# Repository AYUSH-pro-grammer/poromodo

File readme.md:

# Poromodo Timer

A mini pomodoro timer powered by a battery. This was designed using KiCad to create a custom PCB. A small case was designed to house the timer board, OLED and movement sensor. The aim of this project is to create an easy to use and easy to build timer that can rotate the display depending on how it is held.

The design includes a 2S Li-Ion battery, 5V buck converter, 0.96 inch OLED and GY-521 module with MPU-6050. The XIAO manages the timer logic and provides Wi-Fi and Bluetooth Low Energy for future features.

## How it works

The battery pack provides approximately 7.4V (8.4V fully charged). This is passed through a power switch and P Channel MOSFET anti polarity protection circuit, then into a 5V Buck converter (AP63205). A Schottky diode is used to feed the 5V rail to the XIAO's VBUS pin. This also helps to prevent USB power being fed into the Buck Converter.

The XIAO has an onboard regulator that provides a 3.3V rail to provide power to the OLED and GY-521 motion sensing module. The OLED uses I2C to communicate with the XIAO. The MPU-6050 uses the same I2C line to send orientation data. This can be used by the firmware to rotate the display. A resistor divider is used to step down the battery voltage to be passed to the ADC. The buttons, status LED and buzzer are all connected to individual GPIO pins. The buzzer is turned on using an NPN transistor.

```text
[ 2S Li-ion Battery ]
          |
          v
[ Power Switch + Reverse-Polarity Protection ]
          |
          v
[ AP63205 Buck Converter ] -- 5 V --> [ Schottky Diode ]
                                               |
                                               v
                                      [ XIAO ESP32-C3 ]
                                         |         |
                                      3.3 V       GPIO / ADC
                                         |         |
                             +-----------+         +------------------+
                             |           |         |        |         |
                             v           v         v        v         v
                          [ OLED ]   [ GY-521 ] [ Buttons ] [ LED ] [ Buzzer ]
                              \\___________ I2C ___________//
```

## Main features

Seeed XIAO ESP32-C3 (Wi-Fi + BLE) micro controller module
2S Li-ion battery input
AP63205 5V buck converter
AO3401A P-channel MOSFET used for reverse polarity protection
0.96" 128x64 SSD1306 I2C OLED display
GY-521 MPU-6050 accelerometer and gyroscope module
Resistor voltage divider for battery sensing
Two buttons for user Input
Status LED
Passive buzzer controlled by transistor
Double sided PCB around 36x82mm
Two part 3D printable housing

## Images

### Schematic

### PCB layout

### PCB 3D view

### Enclosure

### PCB quotation

## Assembly guide

The design data, manufacturing data, and housing designs can be found here. Before assembly ensure that component footprints match, and that the pin layout of the connectors matches the OLED and GY-521 modules you have. Different variants may show different pin outs.

PCB Preparation: Order the PCB by using gerber.zip, or each file in gerber/. Ensure that the board outline, drilling and layer detection all look correct.
Board Inspection: Check the board has no obvious damage. Check the pads, connectors, and solder mask. Check for any unexpected short circuits using a multi-meter.
Power Assembly: Construct the battery input, AO3401A protection circuit, AP63205 regulator, inductor, and associated capacitors. Ensure that the MOSFET and regulator are placed correctly (Check pin out of MOSFET and regulator from datasheet).
XIAO Module: Place the module onto the PCB ensuring that the module matches the footprint on the PCB. Check all solder joints. Ensure there are no solder bridges between adjacent pads.
Connector & Peripheral Assembly: Attach the OLED and GY-521 sockets, buttons, LED, buzzer, and battery connector. Check the header pins on the OLED match GND, 3V3, SCL, SDA. Check this matches the display module you have.
Power Rails: Double check everything looks good. If possible use a current limited bench PSU to ensure that the 5V and 3.3V rails are correct.
Housing Assembly: The housing can be found in the 3d/ directory. This contains STEP assembly, Fusion 360 archive, and print ready STLs. Have a test fit of the PCB and OLED. The holes are designed to take M3 hardware.
Battery Connection: Use an appropriate 2S protected battery pack. Ensure you use a proper 2S charger. A fully charged 2S battery will be 8.4V. The XIAO will not use the 1 cell battery input.

## Firmware upload

The `firmware/` directory contains separate Arduino sketches. They are intended to be uploaded one at a time while bringing up and testing the board.

| Sketch | Purpose |
|---|---|
| `01_hello_pins.ino` | Basic GPIO and pin checks |
| `02_i2c_scanner.ino` | Scan the I2C bus for connected devices |
| `03_oled_basics.ino` | Basic OLED initialization and display test |
| `04_oled_animations.ino` | OLED animation tests |
| `05_mpu_config.ino` | MPU-6050 configuration and sensor readings |
| `06_auto_rotate.ino` | Display rotation based on sensor orientation |
| `07_buzzer_buttons_led.ino` | Test the buzzer, buttons and status LED |
| `08_battery_monitor.ino` | Read the battery-voltage divider using the ADC |
| `09_pomodoro_demo.ino` | Combined Pomodoro timer demonstration |

### Upload steps

Install the Arduino IDE.
From within the Boards Manager, install the ESP32 board package from Espressif.
Connect the XIAO ESP32-C3 via USB data cable.
Open one of the .ino files located in firmware/.
Select the board type as XIAO_ESP32C3 and select the correct serial port.
Ensure that all libraries required by the sketch have been installed. These can be seen at the top of each source file.
Click the verify button to compile the sketch. Then click upload.
If the sketch uses serial output, open the Serial Monitor and select the baud rate set in the sketch.

We will start by using 01_hello_pins.ino. Once we know that the I2C and OLED are working we can move onto the sensor and full demo. Each of these are individual test programs so uploading a new sketch will overwrite the previous firmware on the XIAO.

## Repository contents

```text
.
├── 3d/              # STEP assembly and printable enclosure files
├── firmware/        # Arduino test sketches and Pomodoro demo
├── gerber/          # PCB Gerber and drill files
├── gerber.zip       # Fabrication upload archive
├── images/          # Main project images
├── kicad/           # KiCad schematic and PCB project
├── bom.csv          # Component list, prices and purchase links
└── README.md
```

## Components and BOM

| Qty | Component | Unit price (USD) | Total (USD) | Buy |
|---:|---|---:|---:|---|
| 1 | XIAO ESP32-C3 (U1) | $5.39 | $5.39 | [RobotShop](https://www.robotshop.com/products/seeedstudio-xiao-esp32c3-tiny-mcu-w-wi-fi-ble) |
| 1 | AP63205WU-7 buck converter, 5 V 2 A, TSOT-26 (U2) | $0.25 | $0.25 | [LCSC](https://www.lcsc.com/product-detail/C2071056.html) |
| 1 | Inductor 4.7 µH, Bourns SRN6045TA-4R7M (L1) | $0.60 | $0.60 | [DigiKey](https://www.digikey.fi/en/products/detail/bourns-inc/SRN6045TA-4R7M/6155104) |
| 2 | Capacitor 22 µF 25 V X5R 1206 (C1, C2) | $0.0595 | $0.12 | [LCSC](https://www.lcsc.com/product-detail/C12891.html) |
| 1 | Capacitor 10 µF 1206 (C4) | $0.05 | $0.05 | [LCSC search](https://www.lcsc.com/search?q=10uF+1206+25V+X5R) |
| 2 | Capacitor 100 nF 0805 (C3, C5) | $0.01 | $0.02 | [LCSC search](https://www.lcsc.com/search?q=100nF+0805+50V) |
| 1 | Resistor 1 kΩ 0805 (R1) | $0.01 | $0.01 | [LCSC search](https://www.lcsc.com/search?q=1k+0805+resistor) |
| 1 | Resistor 100 kΩ 0805 (R2, battery divider top) | $0.01 | $0.01 | [LCSC search](https://www.lcsc.com/search?q=100k+0805+resistor) |
| 1 | Resistor 33 kΩ 0805 (R3, battery divider bottom) | $0.01 | $0.01 | [LCSC search](https://www.lcsc.com/search?q=33k+0805+resistor) |
| 1 | Resistor 470 Ω 0805 (R4) | $0.01 | $0.01 | [LCSC search](https://www.lcsc.com/search?q=470+ohm+0805+resistor) |
| 1 | Schottky diode SS34, SMA (D2) | $0.05 | $0.05 | [LCSC search](https://www.lcsc.com/search?q=SS34) |
| 1 | Diode 1N4148W, SOD-123 (D1, buzzer flyback) | $0.02 | $0.02 | [LCSC search](https://www.lcsc.com/search?q=1N4148W) |
| 1 | LED 0805 (D3) | $0.03 | $0.03 | [LCSC search](https://www.lcsc.com/search?q=led+0805) |
| 1 | NPN transistor MMBT3904, SOT-23 (Q1) | $0.02 | $0.02 | [LCSC search](https://www.lcsc.com/search?q=MMBT3904) |
| 1 | P-MOSFET AO3401A, SOT-23 (Q2) | $0.10 | $0.10 | [LCSC search](https://www.lcsc.com/search?q=AO3401A) |
| 1 | Passive buzzer 12 × 9.5 mm, Soberton WT-1209T (BZ1) | $1.15 | $1.15 | [DigiKey](https://www.digikey.com/en/products/detail/soberton-inc/WT-1209T/16384509) |
| 1 | GY-521 MPU6050 module (J4 socket) | $3.79 | $3.79 | [OpenELAB](https://openelab.com/products/mpu6050-gy521-six-axis-sensor) |
| 1 | 0.96-inch OLED 128 × 64 I2C SSD1306, 4-pin (J1 socket) | $6.89 | $6.89 | [ShillehTek](https://shillehtek.com/products/0-96-i2c-white-oled-display-module-4-pin-ssd1306) |
| 1 | Female pin socket 1 × 8, 2.54 mm (J4) | $0.15 | $0.15 | [LCSC search](https://www.lcsc.com/search?q=female+header+1x8+2.54) |
| 1 | Female pin socket 1 × 4, 2.54 mm (J1) | $0.10 | $0.10 | [LCSC search](https://www.lcsc.com/search?q=female+header+1x4+2.54) |
| 1 | Male pin header 1 × 2, 2.54 mm (SW2 footprint) | $0.05 | $0.05 | [LCSC search](https://www.lcsc.com/search?q=pin+header+1x2+2.54) |
| 1 | Slide or rocker switch SPST, wired to SW2 | $0.50 | $0.50 | [LCSC search](https://www.lcsc.com/search?q=slide+switch+SPDT) |
| 2 | Tactile switch 6 × 6 mm through-hole (SW1, SW3) | $0.017 | $0.03 | [LCSC](https://www.lcsc.com/product-detail/C480288.html) |
| 1 | JST PH 2-pin header B2B-PH-K-S (J2) | $0.30 | $0.30 | [DigiKey](https://www.digikey.nl/en/products/detail/jst-sales-america-inc/B2B-PH-K-S/926611) |
| 1 | 2S Li-ion battery pack, 7.4 V, JST PH 2.0 plug | $9.00 | $9.00 | [DigiKey search](https://www.digikey.com/en/search?keywords=7.4V%20li-ion%20battery%20pack%20JST%20PH) |
| 1 | M3 screws and standoffs (4 sets) | $1.50 | $1.50 | [LCSC search](https://www.lcsc.com/search?q=M3+standoff) |
| 1 | PCB, 2-layer, 36 × 82 mm, 1.6 mm, green (5 pieces) | $4.00 | $4.00 | [JLCPCB](https://jlcpcb.com/) |
| 1 | PCB shipping, UPS Express Saver (2–4 business days) | $26.60 | $26.60 | [JLCPCB](https://jlcpcb.com/) |
|  | **Total procurement estimate** |  | **$60.75** |  |

## PCB manufacturing files

The `gerber/` folder contains the exported copper, solder mask, paste, silkscreen, board outline and drill files. The `gerber.zip` archive is provided for uploading to a PCB manufacturer. Review the fabrication preview and confirm the detected board outline, layer count and drill files before ordering.

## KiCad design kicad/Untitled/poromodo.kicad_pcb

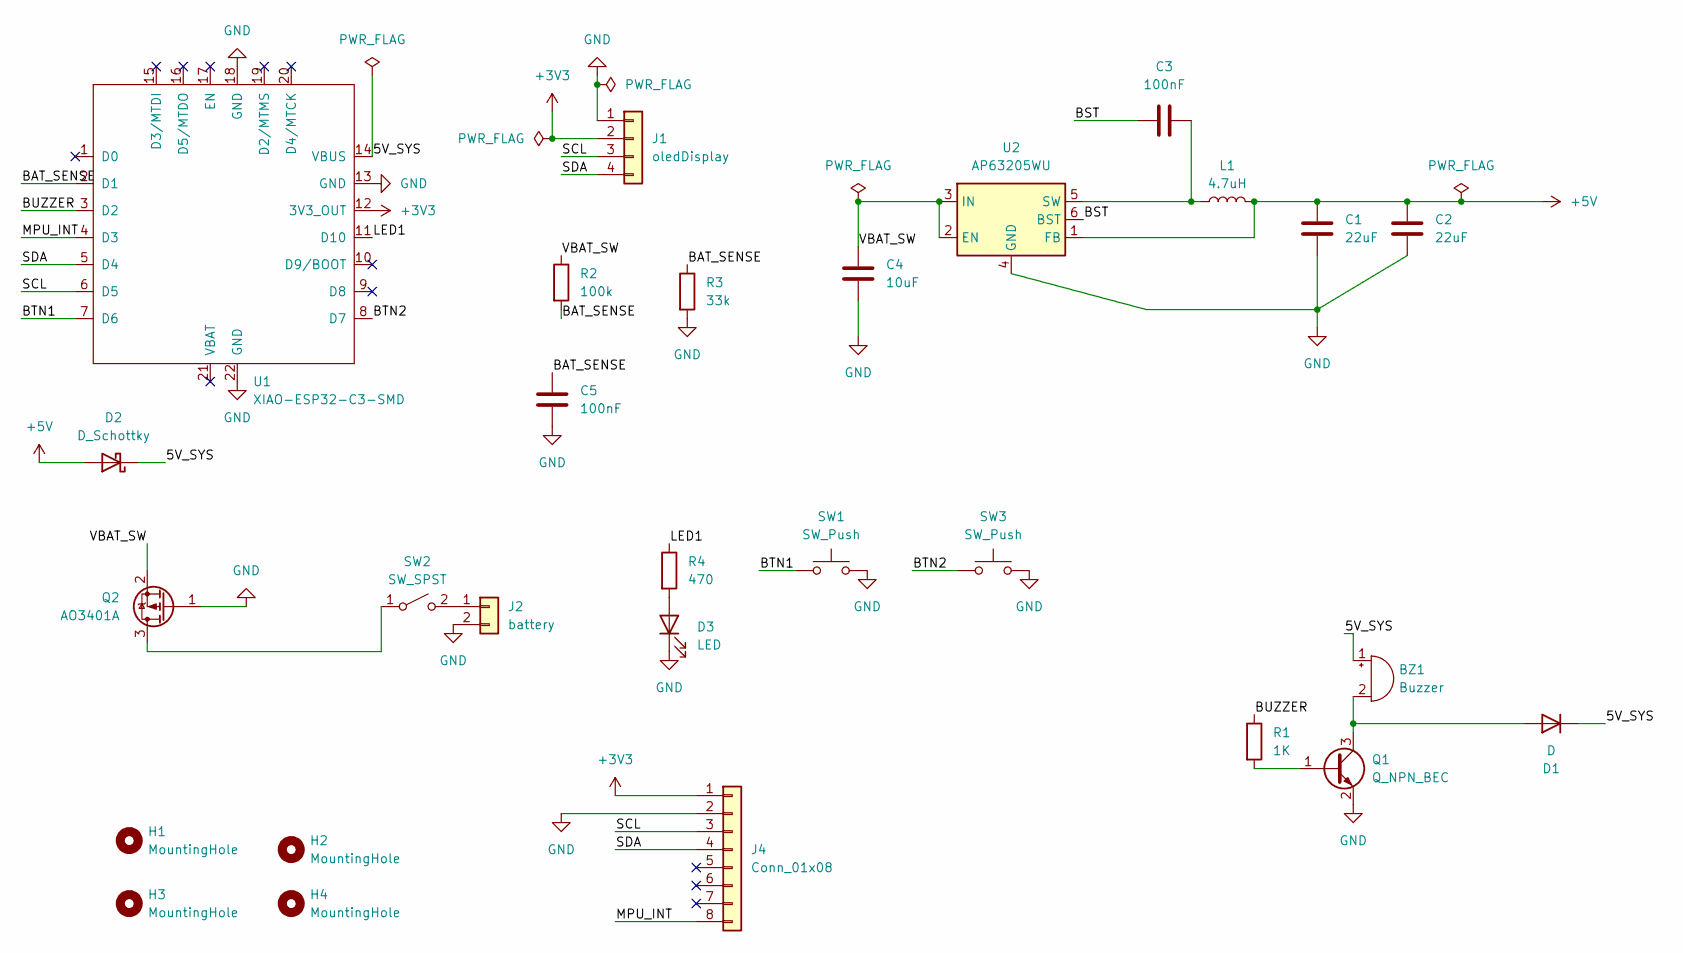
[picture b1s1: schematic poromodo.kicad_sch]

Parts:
BZ1: Buzzer; Buzzer_12x9.5RM7.6
C1, C2: 22uF; C_1206_3216Metric
C3, C5: 100nF; C_0805_2012Metric
C4: 10uF; C_1206_3216Metric
D1: D; D_SOD-123
D2: D_Schottky; D_SMA
D3: LED; LED_0805_2012Metric
H1, H2, H3, H4: MountingHole; MountingHole_3.2mm_M3
J1: oledDisplay; PinSocket_1x04_P2.54mm_Vertical
J2: battery; JST_PH_B2B-PH-K_1x02_P2.00mm_Vertical
J4: Conn_01x08; PinSocket_1x08_P2.54mm_Vertical
L1: 4.7uH; L_Bourns_SRN6045TA
Q1: Q_NPN_BEC; SOT-23
Q2: AO3401A; SOT-23
R1: 1K; R_0805_2012Metric
R2: 100k; R_0805_2012Metric
R3: 33k; R_0805_2012Metric
R4: 470; R_0805_2012Metric
SW1, SW3: SW_Push; SW_PUSH_6mm
SW2: SW_SPST; PinHeader_1x02_P2.54mm_Vertical
U1: XIAO-ESP32-C3-SMD
U2: AP63205WU; TSOT-23-6

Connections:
+3V3: J1.2, J4.1, U1.12 (3V3_OUT)
+5V: C1.1, C2.1, D2.2 (A), L1.2, U2.1 (FB)
/5V_SYS: BZ1.1 (+), D1.1 (K), D2.1 (K), U1.14 (VBUS)
/BAT_SENSE: C5.1, R2.2, R3.1, U1.2 (D1)
/BST: C3.1, U2.6 (BST)
/BTN1: SW1.1, U1.7 (D6)
/BTN2: SW3.1, U1.8 (D7)
/BUZZER: R1.1, U1.3 (D2)
/LED1: R4.1, U1.11 (D10)
/MPU_INT: J4.8, U1.4 (D3)
/SCL: J1.3, J4.3, U1.6 (D5)
/SDA: J1.4, J4.4, U1.5 (D4)
/VBAT_SW: C4.1, Q2.2 (S), R2.1, U2.2 (EN), U2.3 (IN)
GND: C1.2, C2.2, C4.2, C5.2, D3.1 (K), J1.1, J2.2, J4.2, Q1.2 (E), Q2.1 (G), R3.2, SW1.2, SW3.2, U1.13 (GND), U1.18 (GND), U1.22 (GND), U2.4 (GND)
unnamed: BZ1.2 (-), D1.2 (A), Q1.3 (C)
unnamed: D3.2 (A), R4.2
unnamed: J2.1, SW2.2 (B)
unnamed: Q1.1 (B), R1.2
unnamed: Q2.3 (D), SW2.1 (A)
unnamed: C3.2, L1.1, U2.5 (SW)

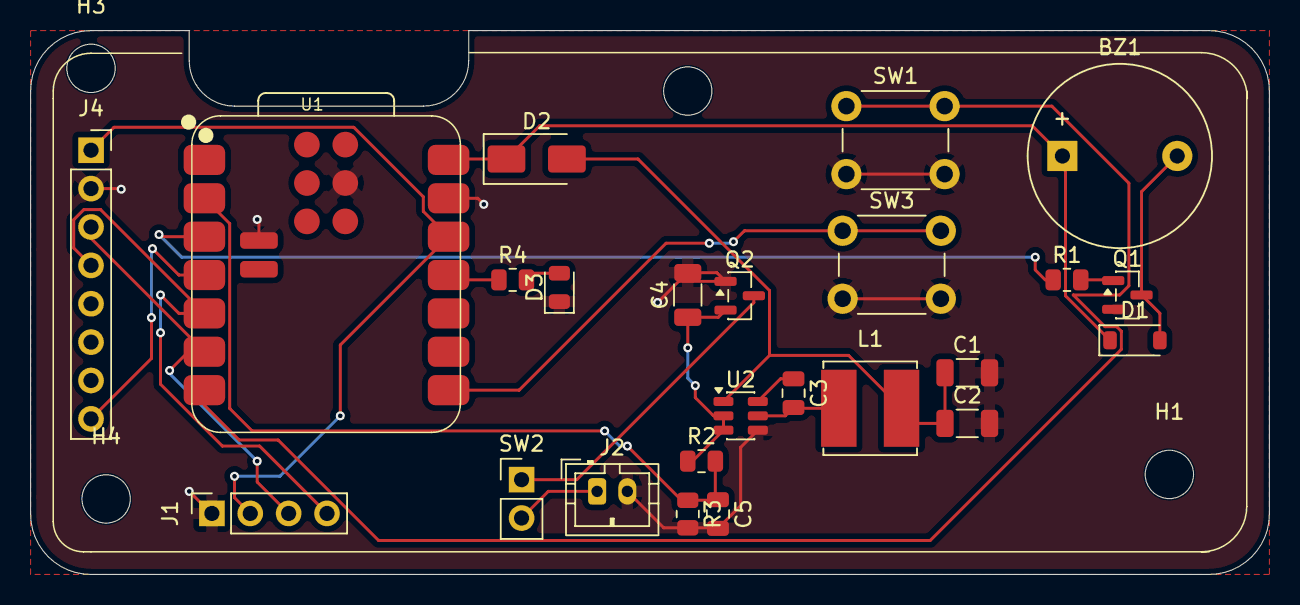
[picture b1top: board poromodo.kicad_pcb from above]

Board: 2 copper layers, 82.0 x 36.0 mm, 28 parts (0 on the bottom side), 20 nets.

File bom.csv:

Name,Quantity,Unit price (USD),Total (USD),URL to buy,Notes
XIAO ESP32-C3 (U1),1,5.39,5.39,https://www.robotshop.com/products/seeedstudio-xiao-esp32c3-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,Seeed XIAO ESP32C3 board only. price checked on seller page
"AP63205WU-7 buck converter, 5V 2A, TSOT-26 (U2)",1,0.25,0.25,https://www.lcsc.com/product-detail/C2071056.html,"LCSC 'from' price, small quantities cost a little more. price checked on seller page"
"Inductor 4.7uH, Bourns SRN6045TA-4R7M (L1)",1,0.60,0.60,https://www.digikey.fi/en/products/detail/bourns-inc/SRN6045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,"Out of stock at DigiKey (18 week lead time). Use a 6x6 mm 4.7uH shielded inductor with the same land pattern. estimate, check at checkout"
"Capacitor 22uF 25V X5R 1206 (C1, C2)",2,0.0595,0.12,https://www.lcsc.com/product-detail/C12891.html,Samsung CL31A226KAHNNNE. LCSC 'from' price. price checked on seller page
Capacitor 10uF 1206 (C4),1,0.05,0.05,https://www.lcsc.com/search?q=10uF+1206+25V+X5R,"Use 16V or higher. estimate, check at checkout"
"Capacitor 100nF 0805 (C3, C5)",2,0.01,0.02,https://www.lcsc.com/search?q=100nF+0805+50V,"Parts are very cheap but often sold in packs. estimate, check at checkout"
Resistor 1k 0805 (R1),1,0.01,0.01,https://www.lcsc.com/search?q=1k+0805+resistor,"estimate, check at checkout"
"Resistor 100k 0805 (R2, battery divider top)",1,0.01,0.01,https://www.lcsc.com/search?q=100k+0805+resistor,"estimate, check at checkout"
"Resistor 33k 0805 (R3, battery divider bottom)",1,0.01,0.01,https://www.lcsc.com/search?q=33k+0805+resistor,"estimate, check at checkout"
Resistor 470 ohm 0805 (R4),1,0.01,0.01,https://www.lcsc.com/search?q=470+ohm+0805+resistor,"estimate, check at checkout"
"Schottky diode SS34, SMA (D2)",1,0.05,0.05,https://www.lcsc.com/search?q=SS34,"estimate, check at checkout"
"Diode 1N4148W, SOD-123 (D1, buzzer flyback)",1,0.02,0.02,https://www.lcsc.com/search?q=1N4148W,"estimate, check at checkout"
LED 0805 (D3),1,0.03,0.03,https://www.lcsc.com/search?q=led+0805,"estimate, check at checkout"
"NPN transistor MMBT3904, SOT-23 (Q1)",1,0.02,0.02,https://www.lcsc.com/search?q=MMBT3904,"estimate, check at checkout"
"P-MOSFET AO3401A, SOT-23 (Q2)",1,0.10,0.10,https://www.lcsc.com/search?q=AO3401A,"estimate, check at checkout"
"Passive buzzer 12x9.5 mm, Soberton WT-1209T (BZ1)",1,1.15,1.15,https://www.digikey.com/en/products/detail/soberton-inc/WT-1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,DigiKey qty 1 price. Check the datasheet for 7.6 mm pin pitch before ordering. price checked on seller page
GY-521 MPU6050 module (J4 socket),1,3.79,3.79,https://openelab.com/products/mpu6050-gy521-six-axis-sensor,Listed as sold out / pre-order (10-20 working days). Check other sellers. price checked on seller page
"0.96 inch OLED 128x64 I2C SSD1306, 4 pin (J1 socket)",1,6.89,6.89,https://shillehtek.com/products/0-96-i2c-white-oled-display-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,"Pin order differs between modules. Check it matches J1 (GND, 3V3, SCL, SDA) or the module will not work. price checked on seller page"
"Female pin socket 1x8, 2.54 mm (J4)",1,0.15,0.15,https://www.lcsc.com/search?q=female+header+1x8+2.54,"estimate, check at checkout"
"Female pin socket 1x4, 2.54 mm (J1)",1,0.10,0.10,https://www.lcsc.com/search?q=female+header+1x4+2.54,"estimate, check at checkout"
"Male pin header 1x2, 2.54 mm (SW2 footprint)",1,0.05,0.05,https://www.lcsc.com/search?q=pin+header+1x2+2.54,"estimate, check at checkout"
"Slide or rocker switch SPST, to wire to SW2",1,0.50,0.50,https://www.lcsc.com/search?q=slide+switch+SPDT,"estimate, check at checkout"
"Tactile switch 6x6 mm through hole (SW1, SW3)",2,0.017,0.03,https://www.lcsc.com/product-detail/C480288.html,"XKB TC-1102-B-I-B, LCSC 'from' price, low stock (280). Pick a height that fits your case. price checked on seller page"
JST PH 2-pin header B2B-PH-K-S (J2),1,0.30,0.30,https://www.digikey.nl/en/products/detail/jst-sales-america-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,"Battery pack needs the mating JST PH plug. estimate, check at checkout"
2S Li-ion battery pack 7.4V with JST PH 2.0 plug,1,9.00,9.00,https://www.digikey.com/en/search?keywords=7.4V%20li-ion%20b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,"Not checked. The connector is rated about 2 A. You also need a 2S charger. estimate, check at checkout"
M3 screws and standoffs (4 sets),1,1.50,1.50,https://www.lcsc.com/search?q=M3+standoff,"Mounting holes are 3.2 mm. estimate, check at checkout"
"PCB, 2 layer, 36x82 mm, 1.6 mm, green (5 pieces)",1,4.00,4.00,https://jlcpcb.com/,"JLCPCB cart price (special offer, 2 day build). See images/jlcpcb-cart.png. Upload gerber.zip"
"PCB shipping, UPS Express Saver (2-4 business days)",1,26.60,26.60,https://jlcpcb.com/,JLCPCB shipping estimate for 0.17 kg. A slower method may cost less at checkout

TOTAL,31,,60.75,,"Sum of the Total column, USD, before tax"
